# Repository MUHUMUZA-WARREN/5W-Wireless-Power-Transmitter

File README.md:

# 5W-Wireless-Power-Transmitter
 5W resonant wireless power transmitter

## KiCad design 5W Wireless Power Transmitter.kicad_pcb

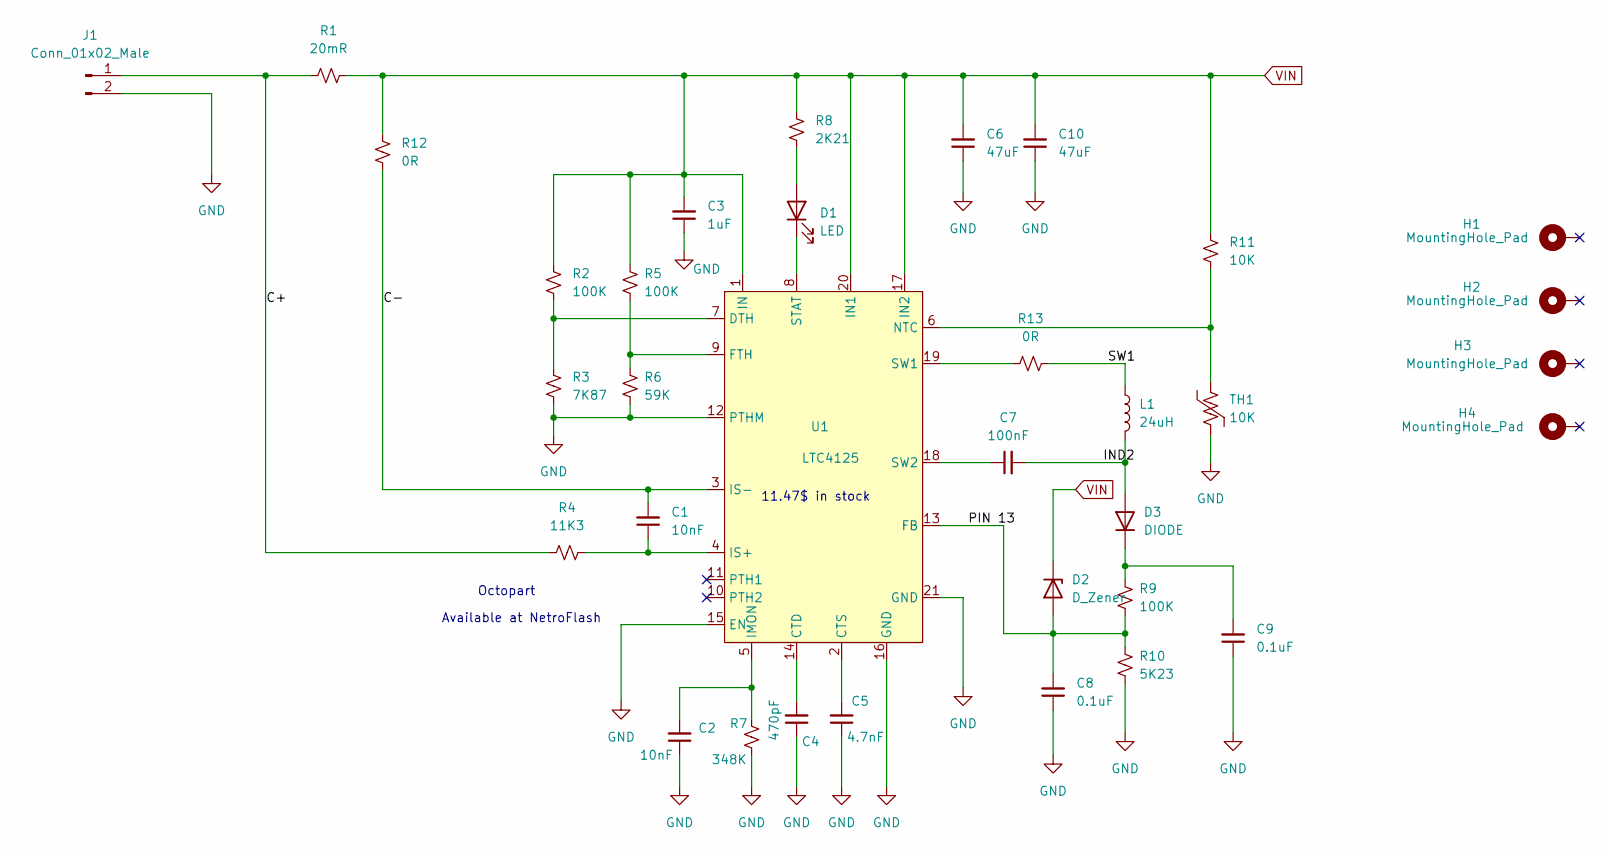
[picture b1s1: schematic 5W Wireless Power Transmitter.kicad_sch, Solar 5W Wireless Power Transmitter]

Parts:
C1, C2: 10nF; C_0805_2012Metric
C3: 1uF; C_1210_3225Metric
C4: 470pF; C_0805_2012Metric
C5: 4.7nF; C_0805_2012Metric
C6, C10: 47uF; C_1210_3225Metric
C7: 100nF; C_0805_2012Metric
C8, C9: 0.1uF; C_0805_2012Metric
D1: LED; LED_D1.8mm_W1.8mm_H2.4mm_Horizontal_O1.27mm_Z1.6mm
D2: D_Zener; D_SOD-523
D3: DIODE; D_SOD-523
H1, H2, H3, H4: MountingHole_Pad; MountingHole_3.5mm_Pad_Via
J1: Conn_01x02_Male; PhoenixContact_GMSTBA_2,5_2-G-7,62_1x02_P7.62mm_Horizontal
L1: 24uH; Tx Coil
R1: 20mR; R_1206_3216Metric
R2, R5: 100K; R_1210_3225Metric
R3: 7K87; R_1210_3225Metric
R4: 11K3; R_0805_2012Metric
R6: 59K; R_1210_3225Metric
R7: 348K; R_0805_2012Metric
R8: 2K21; R_1210_3225Metric
R9: 100K; R_0805_2012Metric
R10: 5K23; R_0805_2012Metric
R11: 10K; R_1210_3225Metric
R12: 0R; R_1206_3216Metric
R13: 0R; R_0805_2012Metric
TH1: 10K; R_1210_3225Metric
U1: LTC4125; QFN-20-1EP_4x5mm_P0.5mm_EP2.65x3.65mm_ThermalVias

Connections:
/C+: J1.1, R1.1, R4.1
/C-: C1.2, R12.1, U1.3 (IS-)
/IND2: C7.2, D3.1 (A), L1.2
/PIN 13: C8.2, D2.2 (A), R9.2, R10.1, U1.13 (FB)
/SW1: L1.1, R13.1
GND: C2.1, C3.1, C4.1, C5.1, C6.1, C8.1, C9.1, C10.1, J1.2, R3.2, R6.2, R7.2, R10.2, TH1.2, U1.12 (PTHM), U1.15 (EN), U1.16 (GND), U1.21 (GND)
unnamed: C1.1, R4.2, U1.4 (IS+)
unnamed: C2.2, R7.1, U1.5 (IMON)
unnamed: C4.2, U1.14 (CTD)
unnamed: C5.2, U1.2 (CTS)
unnamed: C7.1, U1.18 (SW2)
unnamed: C9.2, D3.2 (K), R9.1
unnamed: D1.1 (K), U1.8 (STAT)
unnamed: D1.2 (A), R8.2
unnamed: R2.2, R3.1, U1.7 (DTH)
unnamed: R5.2, R6.1, U1.9 (FTH)
unnamed: R11.2, TH1.1, U1.6 (NTC)
unnamed: R13.2, U1.19 (SW1)
VIN: C3.2, C6.2, C10.2, D2.1 (K), R1.2, R2.1, R5.1, R8.1, R11.1, R12.2, U1.1 (IN), U1.17 (IN2), U1.20 (IN1)

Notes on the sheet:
Available at NetroFlash
Octopart
11.47$ in stock

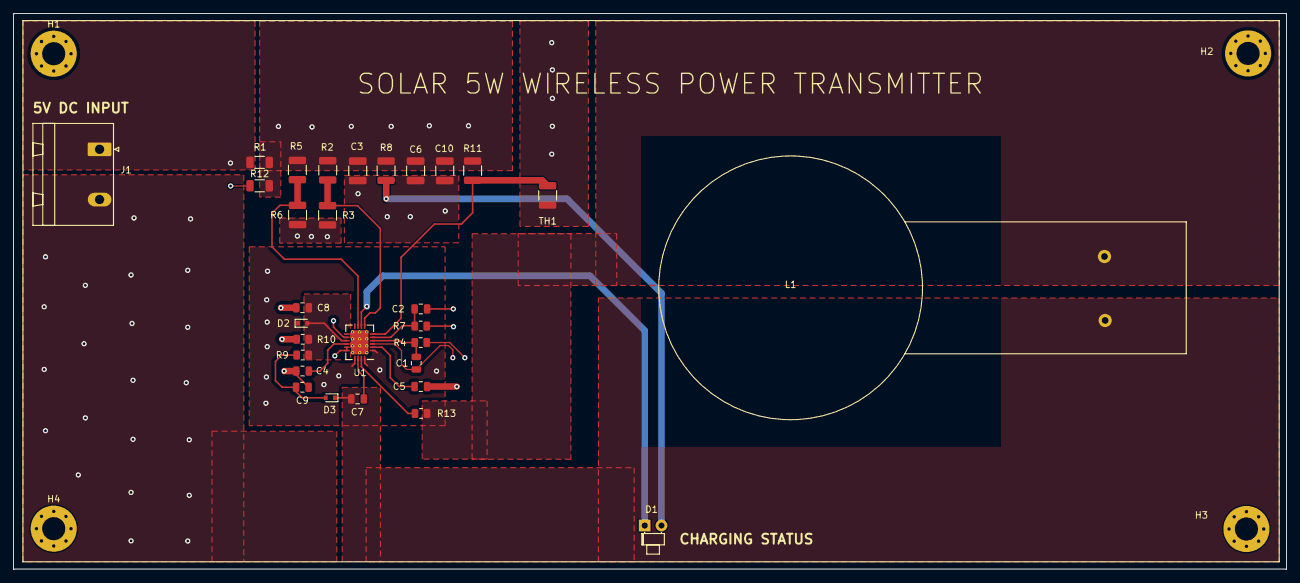
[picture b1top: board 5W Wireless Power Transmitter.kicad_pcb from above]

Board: 4 copper layers, 193.1 x 84.2 mm, 34 parts (0 on the bottom side), 19 nets.

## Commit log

2024-11-05 Create .gitignore
    Created a gitignore for backup files.
2024-11-05 Update README.md
    Added an image to the readme file.
